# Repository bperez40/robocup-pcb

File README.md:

RoboCup PCB Repository
===========
Welcome to the Georgia Tech RoboJackets repository for management and storage of RoboCup's hardware files! Additional information about the team and current projects can be found on the [RoboJackets Website](http://www.robojackets.org/teams/robocup/) and the [RoboJacket Wiki](http://wiki.robojackets.org/w/RoboCup).

If you are a new member to the RoboCup electrical team and have never used *[git version control](http://git-scm.com/)* before, we highly recommend that you familiarize yourself with it by reading [this guide](https://github.com/RoboJackets/robocup-firmware/blob/master/doc/Git.md).

## Sponsor Thank You!
- Maxon (discount of EC45 and EC16 motors)
- PCBWay (donation of PCB fabrication runs)
- Texas Instruments (donation of ICs and SBCs)

## Prerequisites
- A computer configured with git [[Windows](https://windows.github.com)] [[Mac](https://mac.github.com/)]
- An installation of [EAGLE](http://www.cadsoftusa.com/)

## Using this Repository
Most CAD files found here are [EAGLE](http://www.cadsoftusa.com/) files. However, very few older archived files were created using [PCB](http://pcb.geda-project.org) (a program that is part of the [gEDA project](http://www.geda-project.org)). Users will find the following items here:
- Control, Kicker, Breakbeam, and Radio files

## Installation
Once your computer is setup with git, the following lines can be used on any operating system within a *[terminal](http://en.wikipedia.org/wiki/Computer_terminal)* configured with git. Users who are using a GUI interface for git should simply add the respective repositories through the interface.

### RoboCup Files
```
# Download the initial files
git clone https://github.com/robojackets/robocup-pcb

# Go into our new directory
cd robocup-pcb

# Download additional mtrain pcbs
git submodule update --init
```

### EAGLE Libraries
```
# Download the initial files
git clone https://github.com/RoboJackets/eagle-libraries.git

# Go into our new directory
cd eagle-libraries

# Follow the README.md file there
```

### Updating Repository
```
# Check which files will removed
git clean -d -x -n

# After being sure which files are deleted
git clean -d -x -f

# Download additional mtrain pcbs
git submodule update --init
```

## License

This project is licensed under the Apache License v2.0.  See the [LICENSE](LICENSE) file for more information.

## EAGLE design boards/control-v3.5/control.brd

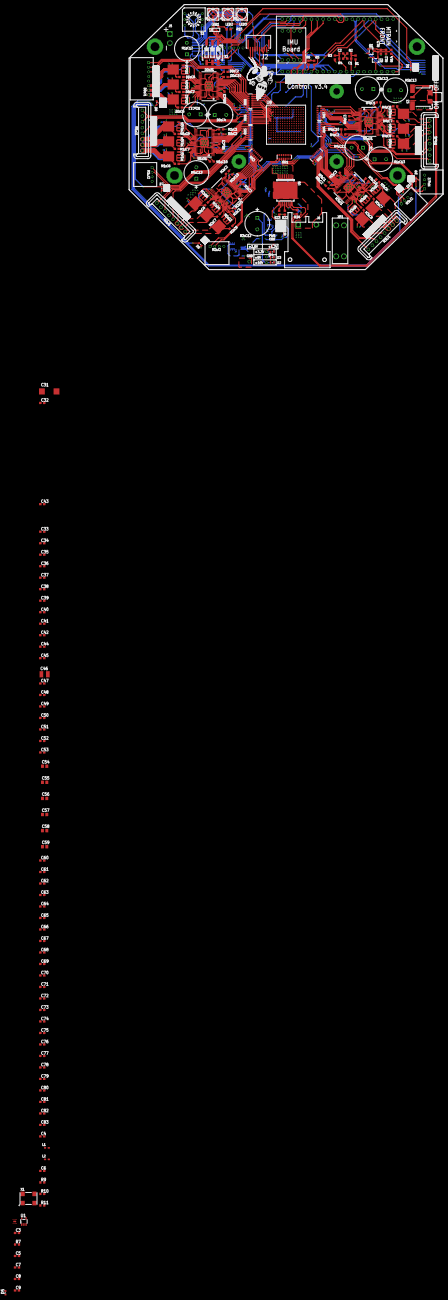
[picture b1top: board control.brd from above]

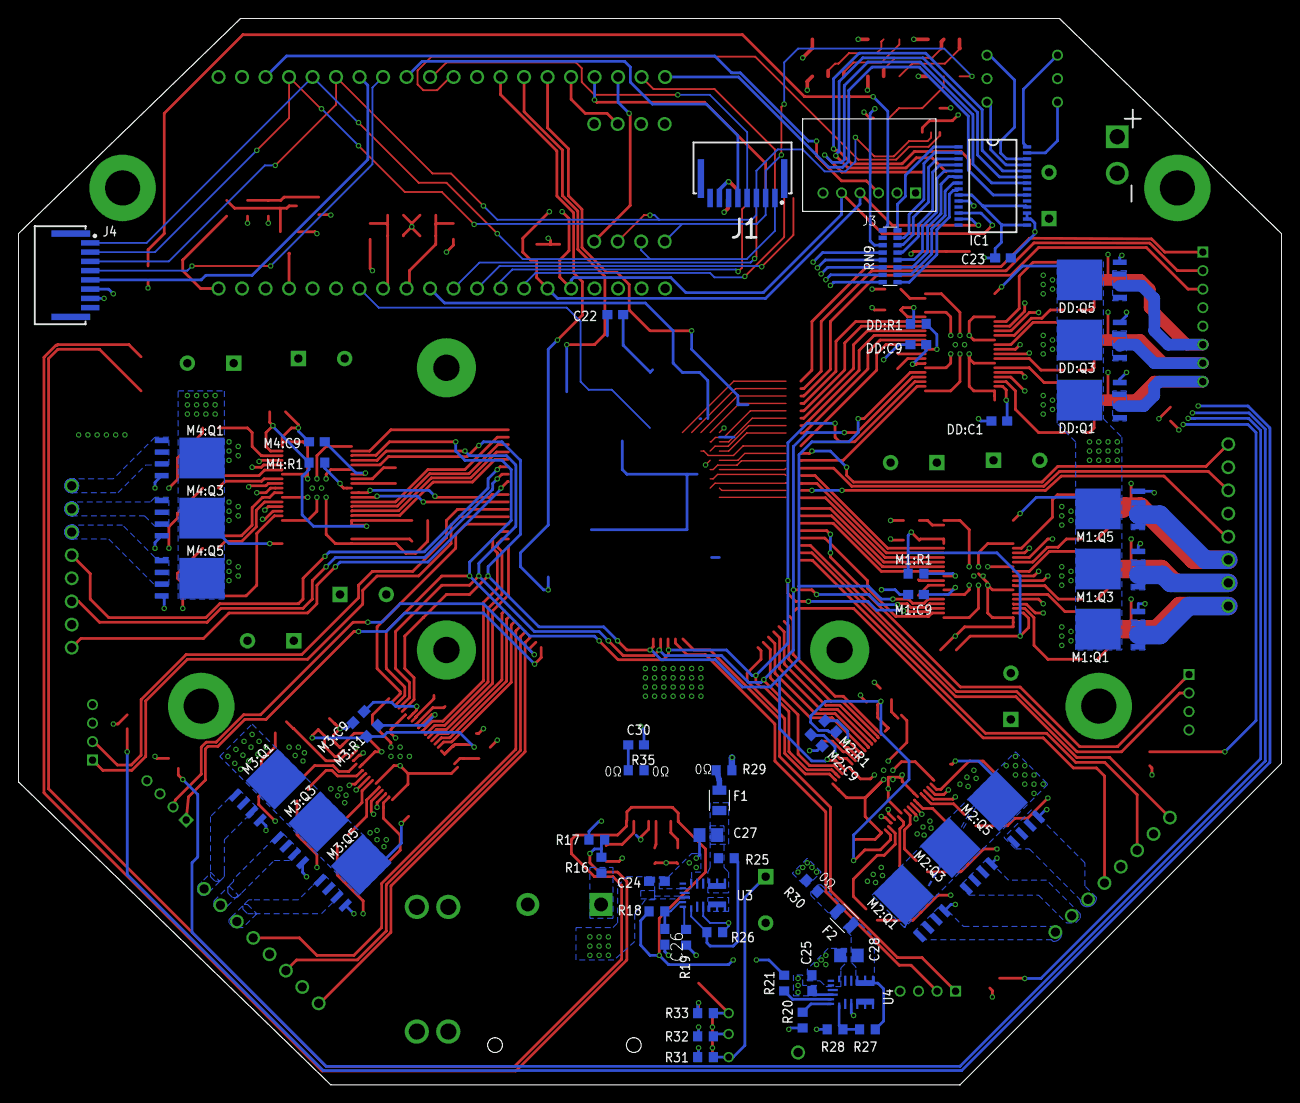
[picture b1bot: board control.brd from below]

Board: 6 copper layers, 136.5 x 115.2 mm, 264 parts (59 on the bottom side), 305 nets.

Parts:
C1: 0.1uF 50V; C0603
C2, C4, C22, C23: 0.1uF; C0603
C3, C8, C30: 1uF; C0603
C5, C7: 1uF X7R; C0603
C6, C38, C39, C40, C41, C42, C43, C44, C45, C47, C48, C49, C50, C51, C61, C62, C63, C64, C65, C66, C67, C68, C69, C70, C71, C72, C76, C77, C80, C81: 0.47uF; C0603
C9, C32, C33, C34, C35, C36, C37, C52, C53, C60, C73, C74, C75, C78, C79, C82, C83: 4.7uF; C0603
C24, C25: 10uF; C0603
C26: 2.2uF 50V; C0603
C27, C28: 22uF 16V; C0805
C31: 330uF; D/7343-31R
C46: 100uF; C1210
C54, C55, C56, C57, C58, C59: 47uF; C0805
D1, D5, D6, D7, D8, D9, D10: RED; CHIP-LED0603
D2, D3, D4: GREEN; CHIP-LED0603
DD:C1, DD:C2: 1uF; C0603
DD:C3: 0.022uF 50V; C0603
DD:C4: ECA-1HHG221; CAP_PAN_10X12.5
DD:C6, DD:C7, DD:C8, DD:C10: 0.1uF 50V; C0603
DD:C9: 2.2uF 50V; C0603
DD:J1: 8-PIN_2MM-H; 2MM-8-H
DD:Q1, DD:Q2, DD:Q3, DD:Q4, DD:Q5, DD:Q6: IRFH7545; PQFN_5X6_E
DD:R1: 10k; R0603
DD:U1: DRV8303DCA; TSSOP-48_PAD
F1, F2: 2A; FUSC2113X75
IC1: MCP23017-E/SS; SSOP-28
J1, J2, J4: HFW8R-1ST
J3: 6-PIN_2MM-H; 2MM-6-H
J5: 2-PIN-KICKERS; B2P_SMALL
J6: DF22-2; DF22-2-H
KIT1: MTRAIN; MTRAIN-KIT
KIT2: IMU
L1, L2: 60Ohm@100MHz; L0603
LED1, LED2, LED3: APA102C-5050; APA102_5050
M1:C1, M1:C2, M2:C1, M2:C2, M3:C1, M3:C2, M4:C1, M4:C2: 1uF; C0603
M1:C3, M2:C3, M3:C3, M4:C3: 0.022uF 50V; C0603
M1:C6, M1:C7, M1:C8, M1:C10, M2:C6, M2:C7, M2:C8, M2:C10, M3:C6, M3:C7, M3:C8, M3:C10, M4:C6, M4:C7, M4:C8, M4:C10: 0.1uF 50V; C0603
M1:C9, M2:C9, M3:C9, M4:C9: 2.2uF 50V; C0603
M1:C12, M1:C13, M2:C12, M2:C13, M3:C12, M3:C13, M4:C12, M4:C13: ECA-1HHG221; CAP_PAN_10X12.5
M1:J1, M2:J1, M3:J1, M4:J1: MKS-1658
M1:J2, M2:J2, M3:J2, M4:J2: 4-PIN_2MM-H; 2MM-4-H
M1:Q1, M1:Q2, M1:Q3, M1:Q4, M1:Q5, M1:Q6, M2:Q1, M2:Q2, M2:Q3, M2:Q4, M2:Q5, M2:Q6, M3:Q1, M3:Q2, M3:Q3, M3:Q4, M3:Q5, M3:Q6, M4:Q1, M4:Q2, M4:Q3, M4:Q4, M4:Q5, M4:Q6: IRFH7545; PQFN_5X6_E
M1:R1, M2:R1, M3:R1, M4:R1: 10k; R0603
M1:U1, M2:U1, M3:U1, M4:U1: DRV8303DCA; TSSOP-48_PAD
Q1, Q2: BSS806NH6327XTSA1; SOT-23-3
R1: 68k 1%; R0603
R2, R3, R4: 10k 1%; R0603
R5, R6, R9, R10: 4.7k; R0603
R7, R29, R30, R35: 0; R0603
R11: 330; R0603
R12, R22: 10k; R0603
R13, R14, R17: 100k; R0603
R15: 50k; R0603
R16: 270k; R0603
R18, R21: 150k; R0603
R19: 43.2k; R0603
R20: 29.4k; R0603
R23, R24, R31, R32, R33: 1k; R0603
R25, R27: 160k 1%; R0603
R26: 30.1k 1%; R0603
R28: 51.0k 1%; R0603
RN1, RN2, RN3, RN4, RN5, RN6, RN7, RN8, RN9: 330; RA-8_2506
S1: 94HCB16T; HEX
S2: 219-03; CTS-219-03
S3: 34EWMSP12M6RT
U1: MCP1824T-1802E/OT; SOT-23-5
U2: SN74AHC1G125; SOT-23-5
U3, U4: MPM3620GQV-P
U5: VND5E006ASPTR-E; POWERSO-16
U6: MIC47100-1.0YML-TR; DFN8_2X2MM
U8: XC7A35T-1FTG256C; BGA256C100P16X16_1700X1700X155
U$1: ERR-DRIB
U$2: ROBOJACKETS
U$3: MOTOR-1
U$4: DRIBBLER
U$5: MOTOR-2
U$6: MOTOR-3
U$7: MOTOR-4
U$8: ERR-M1
U$9: KICKER
U$11: ROBOBUZZ_1.0X2
U$12: ERR-M2
U$13: ERR-M3
U$14: ERR-M4
U$15: ERR-KICK
X1: ASV-50.000MHZ-E-T; ASV
XF1: 30A; 3557-2

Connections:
5V-LED: D3.A, R32.2
5V-LED1: D4.A, R33.2
18.5V-LED: D2.A, R31.1
!CS!-DOT: KIT1.P$11, U2.1
!CS!-FPGA: KIT1.P$31, U8.K12
!CS!-ICM: KIT1.P$18, KIT2.4
!CS!-KICKER: J4.4, KIT1.P$8
!CS!-RADIO: J2.5, KIT1.P$17
!CS!-SPI: J1.4, KIT1.P$10
!RST!-I2C: J3.2, RN9.11
!RST!-KICKER: J4.5, KIT1.P$7
!RST!-NETWORK: KIT1.!RST, Q2.3
!RST!-RADIO: J2.6, KIT1.P$19
!RST!-SPI: J1.5, KIT1.P$9
!RST!_CTRL: Q1.3, Q2.1, R14.1
+1.0V: C31.+, C32.1, C33.1, C34.1, C35.1, C36.1, C37.1, C38.1, C39.1, C40.1, C41.1, C42.1, C43.1, C44.1, C45.1, C46.1, C47.1, C48.1, R7.2, U8.E10, U8.F7, U8.F9, U8.F11, U8.G6, U8.H9, U8.J6, U8.K9, U8.L8
+1.8V: L2.2, R35.2
+3.3V: C3.1, C7.1, C8.1, C56.1, C61.1, C65.1, C80.1, C81.1, C82.1, C83.1, D5.A, J1.8, R9.2, R10.2, R11.2, U6.P$2, U6.P$5, U6.P$6, U8.E7, U8.L16, U8.M9, U8.M10, U8.M11, U8.M13, U8.N10, U8.P7, U8.R14, U8.T11
+3.3V-FUSE: C28.1, F2.1, R27.2, U4.789
+5V: DD:J1.5, J2.1, J3.1, KIT1.VIN, LED1.1, LED2.1, LED3.1, M1:J1.4, M1:J2.4, M2:J1.4, M2:J2.4, M3:J1.4, M3:J2.4, M4:J1.4, M4:J2.4, R3.1, R29.2, R32.1
+5V-FUSE: C27.1, F1.1, R25.2, U3.789
+18.5V: C24.1, C25.1, DD:C4.1, DD:Q1.5678, DD:Q3.5678, DD:Q5.5678, DD:U1.25, M1:C12.1, M1:C13.1, M1:Q1.5678, M1:Q3.5678, M1:Q5.5678, M1:U1.25, M2:C12.1, M2:C13.1, M2:Q1.5678, M2:Q3.5678, M2:Q5.5678, M2:U1.25, M3:C12.1, M3:C13.1, M3:Q1.5678, M3:Q3.5678, M3:Q5.5678, M3:U1.25, M4:C12.1, M4:C13.1, M4:Q1.5678, M4:Q3.5678, M4:Q5.5678, M4:U1.25, R1.1, R31.2, U3.16, U4.16, XF1.3, XF1.4
AAM: R19.2, U3.18
AAM1: R20.2, U4.18
BATT_PWR_AVAIL: Q1.1, R12.1, R13.2
CS1: R23.2, U5.10
CS2: R24.2, U5.15
CS-DIS: R22.2, U5.12
DD-!CS: DD:U1.4, RN6.11
DD-A-H: DD:U1.13, RN6.9
DD-A-L: DD:U1.14, RN8.16
DD-B-H: DD:U1.15, RN8.15
DD-B-L: DD:U1.16, RN8.14
DD-C-H: DD:U1.17, RN8.13
DD-C-L: DD:U1.18, RN8.12
DD-H1: DD:J1.3, RN8.11
DD-H2: DD:J1.2, RN8.10
DD-H3: DD:J1.1, RN8.9
DD:AVDD: DD:C2.1, DD:U1.23
DD:BST-A: DD:C6.1, DD:U1.44
DD:BST-B: DD:C7.1, DD:U1.39
DD:BST-C: DD:C8.1, DD:U1.34
DD:CP1: DD:C3.1, DD:U1.10
DD:CP2: DD:C3.2, DD:U1.11
DD:EN-GATE: DD:R1.2, DD:U1.12
DD:GH-A: DD:Q1.4, DD:U1.43
DD:GH-B: DD:Q3.4, DD:U1.38
DD:GH-C: DD:Q5.4, DD:U1.33
DD:GL-A: DD:Q2.4, DD:U1.41
DD:GL-B: DD:Q4.4, DD:U1.36
DD:GL-C: DD:Q6.4, DD:U1.31
DD:GVDD: DD:C9.1, DD:U1.9
DD:PHASE-A: DD:C6.2, DD:J1.8, DD:Q1.1, DD:Q1.2, DD:Q1.3, DD:Q2.5678, DD:U1.42
DD:PHASE-B: DD:C7.2, DD:J1.7, DD:Q3.1, DD:Q3.2, DD:Q3.3, DD:Q4.5678, DD:U1.37
DD:PHASE-C: DD:C8.2, DD:J1.6, DD:Q5.1, DD:Q5.2, DD:Q5.3, DD:Q6.5678, DD:U1.32
DIP-1: IC1.22, S2.1
DIP-2: IC1.23, S2.2
DIP-3: IC1.24, S2.3
DOT-CLK-1: LED1.5, R15.2, U2.4
DOT-CLK-1-2: LED1.2, LED2.5
DOT-CLK-2-3: LED2.2, LED3.5
DOT-MOSI-1-2: LED1.3, LED2.4
DOT-MOSI-2-3: LED2.3, LED3.4
EN: C26.1, R18.2, U3.17
EN1: R21.2, U4.17
EN-PWR: R18.1, R21.1, S3.2, U5.9, U5.16
EN-PWR-PRE: R16.1, R17.2, S3.1
EXT_SCK: U8.A9, X1.3
FB: R25.1, R26.2, U3.1
FB1: R27.1, R28.2, U4.1
FPGA-DONE: KIT1.P$15, R11.1, U8.H10
FPGA-INIT: KIT1.P$14, R9.1, U8.K10
FPGA-PROG: KIT1.P$13, R10.1, U8.L9
GND: C1.2, C2.2, C3.2, C5.2, C7.2, C8.2, C9.2, C22.2, C23.2, C24.2, C25.2, C26.2, C27.2, C28.2, C30.2, C31.-, C32.2, C33.2, C34.2, C35.2, C36.2, C37.2, C38.2, C39.2, C40.2, C41.2, C42.2, C43.2, C44.2, C45.2, C46.2, C47.2, C48.2, C49.2, C50.2, C51.2, C52.2, C53.2, C54.2, C55.2, C56.2, C57.2, C58.2, C59.2, C60.2, C61.2, C62.2, C63.2, C64.2, C65.2, C66.2, C67.2, C68.2, C69.2, C70.2, C71.2, C72.2, C73.2, C74.2, C75.2, C76.2, C77.2, C78.2, C79.2, C80.2, C81.2, C82.2, C83.2, D2.C, D3.C, D4.C, DD:C1.2, DD:C2.2, DD:C4.2, DD:C9.2, DD:C10.2, DD:J1.4, DD:Q2.1, DD:Q2.2, DD:Q2.3, DD:Q4.1, DD:Q4.2, DD:Q4.3, DD:Q6.1, DD:Q6.2, DD:Q6.3, DD:U1.3, DD:U1.8, DD:U1.20, DD:U1.24, DD:U1.30, DD:U1.35, DD:U1.40, DD:U1.46, DD:U1.47, DD:U1.48, DD:U1.PAD, IC1.10, IC1.16, IC1.17, J1.7, J2.2, J3.6, J4.6, J5.1, J6.2, KIT1.GND, KIT2.5, L1.2, LED1.6, LED2.6, LED3.6, M1:C1.2, M1:C2.2, M1:C9.2, M1:C10.2, M1:C12.2, M1:C13.2, M1:J1.2, M1:J2.3, M1:Q2.1, M1:Q2.2, M1:Q2.3, M1:Q4.1, M1:Q4.2, M1:Q4.3, M1:Q6.1, M1:Q6.2, M1:Q6.3, M1:U1.3, M1:U1.8, M1:U1.24, M1:U1.30, M1:U1.35, M1:U1.40, M1:U1.46, M1:U1.47, M1:U1.48, M1:U1.PAD, M2:C1.2, M2:C2.2, M2:C9.2, M2:C10.2, M2:C12.2, M2:C13.2, M2:J1.2, M2:J2.3, M2:Q2.1, M2:Q2.2, M2:Q2.3, M2:Q4.1, M2:Q4.2, M2:Q4.3, M2:Q6.1, M2:Q6.2, M2:Q6.3, M2:U1.3, M2:U1.8, M2:U1.24, M2:U1.30, M2:U1.35, M2:U1.40, M2:U1.46, M2:U1.47, M2:U1.48, M2:U1.PAD, M3:C1.2, M3:C2.2, M3:C9.2, M3:C10.2, M3:C12.2, M3:C13.2, M3:J1.2, M3:J2.3, M3:Q2.1, M3:Q2.2, M3:Q2.3, M3:Q4.1, M3:Q4.2, M3:Q4.3, M3:Q6.1, M3:Q6.2, M3:Q6.3, M3:U1.3, M3:U1.8, M3:U1.24, M3:U1.30, M3:U1.35, M3:U1.40, M3:U1.46, M3:U1.47, M3:U1.48, M3:U1.PAD, M4:C1.2, M4:C2.2, M4:C9.2, M4:C10.2, M4:C12.2, M4:C13.2, M4:J1.2, M4:J2.3, M4:Q2.1, M4:Q2.2, M4:Q2.3, M4:Q4.1, M4:Q4.2, M4:Q4.3, M4:Q6.1, M4:Q6.2, M4:Q6.3, M4:U1.3, M4:U1.8, M4:U1.24, M4:U1.30, M4:U1.35, M4:U1.40, M4:U1.46, M4:U1.47, M4:U1.48, M4:U1.PAD, Q1.2, Q2.2, R2.2, R4.2, R13.1, R15.1, R17.1, R19.1, R20.1, R22.1, R23.1, R24.1, R26.1, R28.1, S1.C1, S1.C2, S2.4, S2.5, S2.6, S3.3, S3.LEG1, S3.LEG3, U1.2, U2.3, U3.3, U3.12, U3.13, U3.14, U4.3, U4.12, U4.13, U4.14, U5.13, U6.P$4, U8.A1, U8.A11, U8.B8, U8.C5, U8.C15, U8.D2, U8.D12, U8.E9, U8.F6, U8.F8, U8.F10, U8.F16, U8.G3, U8.G9, U8.G13, U8.H6, U8.H8, U8.J7, U8.J9, U8.J11, U8.K4, U8.K6, U8.K7, U8.K8, U8.K14, U8.L1, U8.L11, U8.L15, U8.M8, U8.N5, U8.N15, U8.P2, U8.P12, U8.R9, U8.T6, U8.T16, X1.2
GNDADC: C4.2, C6.2, L1.1, U8.G7, U8.H7, U8.J8
GPB0: IC1.1, RN9.8
GPB1: IC1.2, RN9.7
GPB2: IC1.3, RN9.6
GPB3: IC1.4, RN9.5
GPB4: IC1.5, RN9.4
GPB5: IC1.6, RN9.3
GPB6: IC1.7, RN9.2
GPB7: IC1.8, RN9.1
HEX-0: IC1.28, S1.1
HEX-1: IC1.25, S1.2
HEX-2: IC1.27, S1.4
HEX-3: IC1.26, S1.8
INT-I2C: J3.3, KIT1.P$3
INT-ICM: KIT1.P$16, KIT2.6
INT-IO: IC1.20, KIT1.P$20
INT-RADIO: J2.4, KIT1.P$30
INT-SPI: J1.6, KIT1.P$12
LED-DD: D8.C, RN9.16
LED-KICK: D1.C, RN9.9
LED-M1: D7.C, RN9.15
LED-M2: D6.C, RN9.14
LED-M3: D10.C, RN9.13
LED-M4: D9.C, RN9.12
M1-!CS: M1:U1.4, RN5.13
M1-A-H: M1:U1.15, RN5.9
M1-A-L: M1:U1.16, RN6.16
M1-B-H: M1:U1.13, RN5.11
M1-B-L: M1:U1.14, RN5.10
M1-C-H: M1:U1.17, RN6.14
M1-C-L: M1:U1.18, RN6.13
M1-ENC-A: M1:J2.2, RN5.14
M1-ENC-B: M1:J2.1, RN5.12
M1-H1: M1:J1.1, RN6.10
M1-H2: M1:J1.3, RN6.12
M1-H3: M1:J1.5, RN6.15
M1:+3.3V: M1:C1.1, M1:C10.1, M1:R1.1, M1:U1.19, M1:U1.20, M1:U1.45
M1:AVDD: M1:C2.1, M1:U1.23
M1:BST-A: M1:C6.1, M1:U1.44
M1:BST-B: M1:C7.1, M1:U1.39
M1:BST-C: M1:C8.1, M1:U1.34
M1:CP1: M1:C3.1, M1:U1.10
M1:CP2: M1:C3.2, M1:U1.11
M1:EN-GATE: M1:R1.2, M1:U1.12
M1:GH-A: M1:Q1.4, M1:U1.43
M1:GH-B: M1:Q3.4, M1:U1.38
M1:GH-C: M1:Q5.4, M1:U1.33
M1:GL-A: M1:Q2.4, M1:U1.41
M1:GL-B: M1:Q4.4, M1:U1.36
M1:GL-C: M1:Q6.4, M1:U1.31
M1:GVDD: M1:C9.1, M1:U1.9
M1:PHASE-A: M1:C7.2, M1:J1.7, M1:Q3.1, M1:Q3.2, M1:Q3.3, M1:Q4.5678, M1:U1.37
M1:PHASE-B: M1:C6.2, M1:J1.8, M1:Q1.1, M1:Q1.2, M1:Q1.3, M1:Q2.5678, M1:U1.42
M1:PHASE-C: M1:C8.2, M1:J1.6, M1:Q5.1, M1:Q5.2, M1:Q5.3, M1:Q6.5678, M1:U1.32
M2-!CS: M2:U1.4, RN3.16
M2-A-H: M2:U1.15, RN3.13
M2-A-L: M2:U1.16, RN3.12
M2-B-H: M2:U1.13, RN3.15
M2-B-L: M2:U1.14, RN3.14
M2-C-H: M2:U1.17, RN3.11
M2-C-L: M2:U1.18, RN3.10
M2-ENC-A: M2:J2.2, RN1.10
M2-ENC-B: M2:J2.1, RN1.9
M2-H1: M2:J1.1, RN5.15
M2-H2: M2:J1.3, RN5.16
M2-H3: M2:J1.5, RN3.9
M2:+3.3V: M2:C1.1, M2:C10.1, M2:R1.1, M2:U1.19, M2:U1.20, M2:U1.45
M2:AVDD: M2:C2.1, M2:U1.23
M2:BST-A: M2:C6.1, M2:U1.44
M2:BST-B: M2:C7.1, M2:U1.39
M2:BST-C: M2:C8.1, M2:U1.34
M2:CP1: M2:C3.1, M2:U1.10
M2:CP2: M2:C3.2, M2:U1.11
M2:EN-GATE: M2:R1.2, M2:U1.12
M2:GH-A: M2:Q1.4, M2:U1.43
M2:GH-B: M2:Q3.4, M2:U1.38
M2:GH-C: M2:Q5.4, M2:U1.33
M2:GL-A: M2:Q2.4, M2:U1.41
M2:GL-B: M2:Q4.4, M2:U1.36
M2:GL-C: M2:Q6.4, M2:U1.31
M2:GVDD: M2:C9.1, M2:U1.9
M2:PHASE-A: M2:C7.2, M2:J1.7, M2:Q3.1, M2:Q3.2, M2:Q3.3, M2:Q4.5678, M2:U1.37
M2:PHASE-B: M2:C6.2, M2:J1.8, M2:Q1.1, M2:Q1.2, M2:Q1.3, M2:Q2.5678, M2:U1.42
M2:PHASE-C: M2:C8.2, M2:J1.6, M2:Q5.1, M2:Q5.2, M2:Q5.3, M2:Q6.5678, M2:U1.32
M3-!CS: M3:U1.4, RN4.12
M3-A-H: M3:U1.15, RN4.9
M3-A-L: M3:U1.16, RN2.16
M3-B-H: M3:U1.13, RN4.11
M3-B-L: M3:U1.14, RN4.10
M3-C-H: M3:U1.17, RN2.15
M3-C-L: M3:U1.18, RN2.14
M3-ENC-A: M3:J2.2, RN2.10
M3-ENC-B: M3:J2.1, RN2.9
M3-H1: M3:J1.1, RN2.11
M3-H2: M3:J1.3, RN2.12
M3-H3: M3:J1.5, RN2.13
M3:+3.3V: M3:C1.1, M3:C10.1, M3:R1.1, M3:U1.19, M3:U1.20, M3:U1.45
M3:AVDD: M3:C2.1, M3:U1.23
M3:BST-A: M3:C6.1, M3:U1.44
M3:BST-B: M3:C7.1, M3:U1.39
M3:BST-C: M3:C8.1, M3:U1.34
M3:CP1: M3:C3.1, M3:U1.10
M3:CP2: M3:C3.2, M3:U1.11
M3:EN-GATE: M3:R1.2, M3:U1.12
M3:GH-A: M3:Q1.4, M3:U1.43
M3:GH-B: M3:Q3.4, M3:U1.38
M3:GH-C: M3:Q5.4, M3:U1.33
M3:GL-A: M3:Q2.4, M3:U1.41
M3:GL-B: M3:Q4.4, M3:U1.36
M3:GL-C: M3:Q6.4, M3:U1.31
M3:GVDD: M3:C9.1, M3:U1.9
M3:PHASE-A: M3:C7.2, M3:J1.7, M3:Q3.1, M3:Q3.2, M3:Q3.3, M3:Q4.5678, M3:U1.37
M3:PHASE-B: M3:C6.2, M3:J1.8, M3:Q1.1, M3:Q1.2, M3:Q1.3, M3:Q2.5678, M3:U1.42
M3:PHASE-C: M3:C8.2, M3:J1.6, M3:Q5.1, M3:Q5.2, M3:Q5.3, M3:Q6.5678, M3:U1.32
M4-!CS: M4:U1.4, RN7.16
M4-A-H: M4:U1.15, RN7.15
M4-A-L: M4:U1.16, RN7.14
M4-B-H: M4:U1.13, RN4.16
M4-B-L: M4:U1.14, RN4.15
M4-C-H: M4:U1.17, RN7.13
M4-C-L: M4:U1.18, RN7.12
M4-ENC-A: M4:J2.2, RN4.14
M4-ENC-B: M4:J2.1, RN4.13
M4-H1: M4:J1.1, RN7.9
M4-H2: M4:J1.3, RN7.10
M4-H3: M4:J1.5, RN7.11
M4:+3.3V: M4:C1.1, M4:C10.1, M4:R1.1, M4:U1.19, M4:U1.20, M4:U1.45
M4:AVDD: M4:C2.1, M4:U1.23
M4:BST-A: M4:C6.1, M4:U1.44
M4:BST-B: M4:C7.1, M4:U1.39
M4:BST-C: M4:C8.1, M4:U1.34
M4:CP1: M4:C3.1, M4:U1.10
M4:CP2: M4:C3.2, M4:U1.11
M4:EN-GATE: M4:R1.2, M4:U1.12
M4:GH-A: M4:Q1.4, M4:U1.43
M4:GH-B: M4:Q3.4, M4:U1.38
M4:GH-C: M4:Q5.4, M4:U1.33
M4:GL-A: M4:Q2.4, M4:U1.41
M4:GL-B: M4:Q4.4, M4:U1.36
M4:GL-C: M4:Q6.4, M4:U1.31
M4:GVDD: M4:C9.1, M4:U1.9
M4:PHASE-A: M4:C7.2, M4:J1.7, M4:Q3.1, M4:Q3.2, M4:Q3.3, M4:Q4.5678, M4:U1.37
M4:PHASE-B: M4:C6.2, M4:J1.8, M4:Q1.1, M4:Q1.2, M4:Q1.3, M4:Q2.5678, M4:U1.42
M4:PHASE-C: M4:C8.2, M4:J1.6, M4:Q5.1, M4:Q5.2, M4:Q5.3, M4:Q6.5678, M4:U1.32
MISO: J1.1, J4.1, KIT1.P$5, KIT2.2
MISO-AUX: DD:U1.6, M1:U1.6, M2:U1.6, M3:U1.6, M4:U1.6, RN1.12
MISO-FPGA: KIT1.P$35, U8.J13
MISO-RADIO: J2.3, KIT1.P$28
MOSI: J1.2, J4.2, KIT1.P$4, KIT2.1, LED1.4
MOSI-AUX: DD:U1.5, M1:U1.5, M2:U1.5, M3:U1.5, M4:U1.5, RN1.11
MOSI-FPGA: KIT1.P$36, U8.J14
MOSI-RADIO: J2.7, KIT1.P$27
unnamed: F2.2, R30.1
unnamed: F1.2, R29.1
unnamed: C5.1, R7.1, U6.P$7, U6.P$8, U6.P$9
PWR-ERR: D5.C, U1.4
SCK: J1.3, J4.3, KIT1.P$6, KIT2.3, U2.2
SCK-AUX: DD:U1.7, M1:U1.7, M2:U1.7, M3:U1.7, M4:U1.7, RN1.13
SCK-FPGA: KIT1.P$34, U8.E8
SCK-RADIO: J2.8, KIT1.P$29
SCL: IC1.12, J3.5, KIT1.P$25, R6.1
SDA: IC1.13, J3.4, KIT1.P$26, R5.1
SENSE-BATTERY: C1.1, KIT1.P$33, R1.2, R2.1
SENSE-VIN: C2.1, KIT1.P$32, R3.2, R4.1
T1: RN2.1, U8.M16
T2: RN2.2, U8.N16
T3: RN2.4, U8.P15
T4: RN2.3, U8.P16
T5: RN2.6, U8.R15
T6: RN2.5, U8.R16
T7: RN2.8, U8.T14
T8: RN2.7, U8.T15
T9: RN7.1, U8.A12
T10: RN7.2, U8.A13
T11: RN7.3, U8.A14
T12: RN7.8, U8.C14
T13: RN7.7, U8.B14
T14: RN7.6, U8.B15
T15: RN7.4, U8.A15
T16: RN7.5, U8.B16
T17: RN4.8, U8.J16
T18: RN4.7, U8.J15
T19: RN4.5, U8.G16
T20: RN4.6, U8.H16
T21: RN4.2, U8.E15
T22: RN4.4, U8.F15
T23: RN4.1, U8.D16
T24: RN4.3, U8.E16
T25: RN8.8, U8.A5
T26: RN8.7, U8.A4
T27: RN8.6, U8.A3
T28: RN8.2, U8.C2
T29: RN8.4, U8.B2
T30: RN8.5, U8.A2
T31: RN8.1, U8.C1
T32: RN8.3, U8.B1
T33: RN6.8, U8.C3
T34: RN6.6, U8.E2
T35: RN6.7, U8.D1
T36: RN6.1, U8.H1
T37: RN6.2, U8.G1
T38: RN6.3, U8.G2
T39: RN6.5, U8.E1
T40: RN6.4, U8.F2
T41: RN5.6, U8.K2
T42: RN5.4, U8.L2
T43: RN5.7, U8.J1
T44: RN5.5, U8.K1
T45: RN5.8, U8.H2
T46: RN5.3, U8.M2
T47: RN5.2, U8.M1
T48: RN5.1, U8.N1
T49: RN3.2, U8.T3
T50: RN3.1, U8.T4
T51: RN3.3, U8.T2
T52: RN3.4, U8.R3
T53: RN3.5, U8.R1
T54: RN3.6, U8.R2
T55: RN3.7, U8.P1
T56: RN3.8, U8.N2
T57: RN1.8, U8.T5
T58: RN1.4, U8.T10
T59: RN1.5, U8.T9
T60: RN1.6, U8.T8
T61: RN1.7, U8.T7
VBATT: J5.2, U5.1, U5.2, U5.3, U5.4, U5.5, U5.6, U5.7, U5.8, XF1.1, XF1.2
VCCAUX: C4.1, C6.1, C49.1, C50.1, C51.1, C52.1, C53.1, C54.1, L2.1, U8.G8, U8.G10, U8.J10, U8.K11, U8.L10
VCCO_0: C9.1, C22.1, C23.1, C55.1, C57.1, C58.1, C59.1, C60.1, C62.1, C63.1, C64.1, C66.1, C67.1, C68.1, C69.1, C70.1, C71.1, C72.1, C73.1, C74.1, C75.1, C76.1, C77.1, C78.1, C79.1, D1.A, D6.A, D7.A, D8.A, D9.A, D10.A, DD:C1.1, DD:C10.1, DD:R1.1, DD:U1.19, DD:U1.45, IC1.9, IC1.15, IC1.18, J4.7, KIT2.8, R5.2, R6.2, R12.2, R30.2, R33.1, U1.1, U1.3, U2.5, U8.A6, U8.A16, U8.B3, U8.B13, U8.C10, U8.D7, U8.E4, U8.E14, U8.F1, U8.H15, U8.J2, U8.J12, U8.L6, U8.M3, U8.R4, U8.T1, X1.1, X1.4
VIN: J6.1, R16.2, U5.17
V_MTRAIN: KIT1.VDD, R14.2
V_OUT: C30.1, R35.1, U1.5

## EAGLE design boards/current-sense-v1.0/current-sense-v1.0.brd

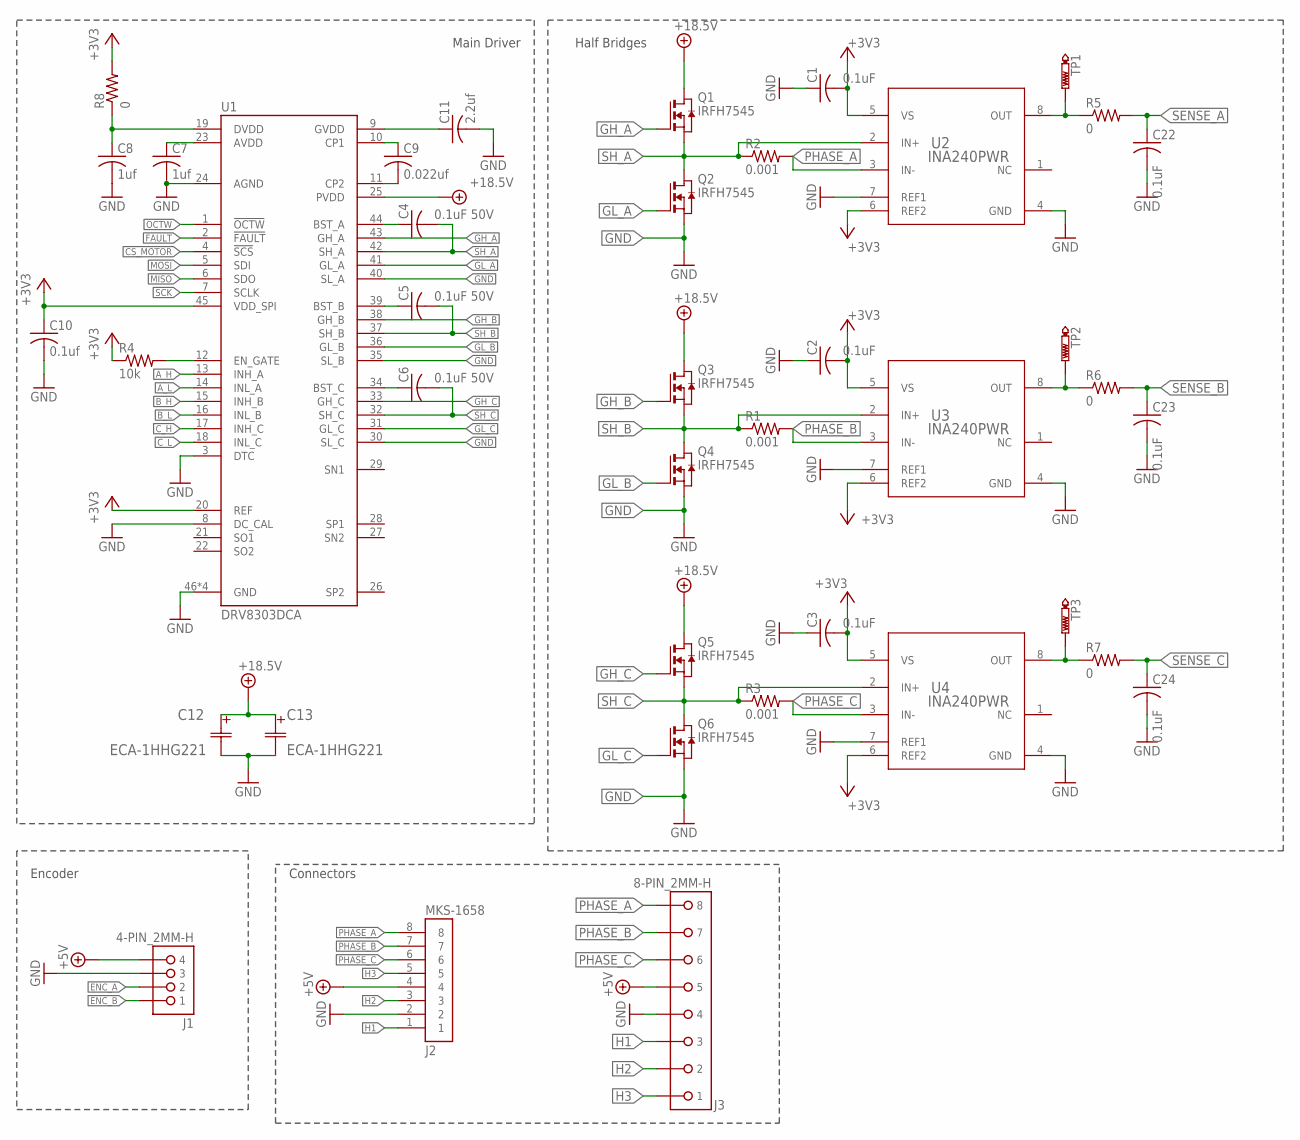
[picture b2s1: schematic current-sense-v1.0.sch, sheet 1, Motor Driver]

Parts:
C1, C2, C3, C22, C23, C24: 0.1uF; C0603
C4, C5, C6: 0.1uF 50V; C0603
C7, C8: 1uf; C0603
C9: 0.022uf; C0603
C10: 0.1uf; C0603
C11: 2.2uf; C0603
C12, C13: ECA-1HHG221; CAP_PAN_10X12.5
J1: 4-PIN_2MM-H; 2MM-4-H
J2: MKS-1658
J3: 8-PIN_2MM-H; 2MM-8-H
Q1, Q2, Q3, Q4, Q5, Q6: IRFH7545; PQFN_5X6_E
R1, R2, R3: 0.001; R2512
R4: 10k; R0603
R5, R6, R7, R8: 0; R0603
TP1, TP2, TP3: PTR1PAD1-13; P1-13
U1: DRV8303DCA; TSSOP-48_PAD
U2, U3, U4: INA240PWR; PW0008A_N

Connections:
+3V3: C1.2, C2.2, C3.2, C10.1, R4.1, R8.2, U1.20 (REF), U1.45 (VDD_SPI), U2.5 (VS), U2.6 (REF2), U3.5 (VS), U3.6 (REF2), U4.5 (VS), U4.6 (REF2); also elsewhere on the board
+5V: J1.4, J2.4, J3.5; also elsewhere on the board
+18.5V: C12.1 (11), C13.1 (11), Q1.5678 (D), Q3.5678 (D), Q5.5678 (D), U1.25 (PVDD); also elsewhere on the board
AVDD: C7.1, U1.23 (AVDD)
A_H: U1.13 (INH_A); also elsewhere on the board
A_L: U1.14 (INL_A); also elsewhere on the board
BST_A: C4.1, U1.44 (BST_A)
BST_B: C5.1, U1.39 (BST_B)
BST_C: C6.1, U1.34 (BST_C)
B_H: U1.15 (INH_B); also elsewhere on the board
B_L: U1.16 (INL_B); also elsewhere on the board
CP1: C9.1, U1.10 (CP1)
CP2: C9.2, U1.11 (CP2)
CS_MOTOR: U1.4 (!SCS); also elsewhere on the board
C_H: U1.17 (INH_C); also elsewhere on the board
C_L: U1.18 (INL_C); also elsewhere on the board
DVDD: C8.1, R8.1, U1.19 (DVDD)
ENC_A: J1.2; also elsewhere on the board
ENC_B: J1.1; also elsewhere on the board
EN_GATE: R4.2, U1.12 (EN_GATE)
FAULT: U1.2 (!FAULT)
GH_A: Q1.4 (G), U1.43 (GH_A)
GH_B: Q3.4 (G), U1.38 (GH_B)
GH_C: Q5.4 (G), U1.33 (GH_C)
GL_A: Q2.4 (G), U1.41 (GL_A)
GL_B: Q4.4 (G), U1.36 (GL_B)
GL_C: Q6.4 (G), U1.31 (GL_C)
GND: C1.1, C2.1, C3.1, C7.2, C8.2, C10.2, C11.2, C12.2 (22), C13.2 (22), C22.2, C23.2, C24.2, J1.3, J2.2, J3.4, Q2.1 (S), Q2.2 (S), Q2.3 (S), Q4.1 (S), Q4.2 (S), Q4.3 (S), Q6.1 (S), Q6.2 (S), Q6.3 (S), U1.3 (DTC), U1.8 (DC_CAL), U1.24 (AGND), U1.30 (SL_C), U1.35 (SL_B), U1.40 (SL_A), U1.46 (GND), U1.47 (GND), U1.48 (GND), U1.PAD (GND), U2.4 (GND), U2.7 (REF1), U3.4 (GND), U3.7 (REF1), U4.4 (GND), U4.7 (REF1); also elsewhere on the board
GVDD: C11.1, U1.9 (GVDD)
H1: J2.1, J3.3; also elsewhere on the board
H2: J2.3, J3.2; also elsewhere on the board
H3: J2.5, J3.1; also elsewhere on the board
MISO: U1.6 (SDO); also elsewhere on the board
MOSI: U1.5 (SDI); also elsewhere on the board
OCTW: U1.1 (!OCTW)
OUT_A: R5.1, TP1.TP, U2.8 (OUT)
OUT_B: R6.1, TP2.TP, U3.8 (OUT)
OUT_C: R7.1, TP3.TP, U4.8 (OUT)
PHASE_A: J2.8, J3.8, R2.2, U2.3 (IN-)
PHASE_B: J2.7, J3.7, R1.2, U3.3 (IN-)
PHASE_C: J2.6, J3.6, R3.2, U4.3 (IN-)
SCK: U1.7 (SCLK); also elsewhere on the board
SENSE_A: C22.1, R5.2; also elsewhere on the board
SENSE_B: C23.1, R6.2; also elsewhere on the board
SENSE_C: C24.1, R7.2; also elsewhere on the board
SH_A: C4.2, Q1.1 (S), Q1.2 (S), Q1.3 (S), Q2.5678 (D), R2.1, U1.42 (SH_A), U2.2 (IN+)
SH_B: C5.2, Q3.1 (S), Q3.2 (S), Q3.3 (S), Q4.5678 (D), R1.1, U1.37 (SH_B), U3.2 (IN+)
SH_C: C6.2, Q5.1 (S), Q5.2 (S), Q5.3 (S), Q6.5678 (D), R3.1, U1.32 (SH_C), U4.2 (IN+)

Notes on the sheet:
Main Driver
Encoder
Connectors
Half Bridges

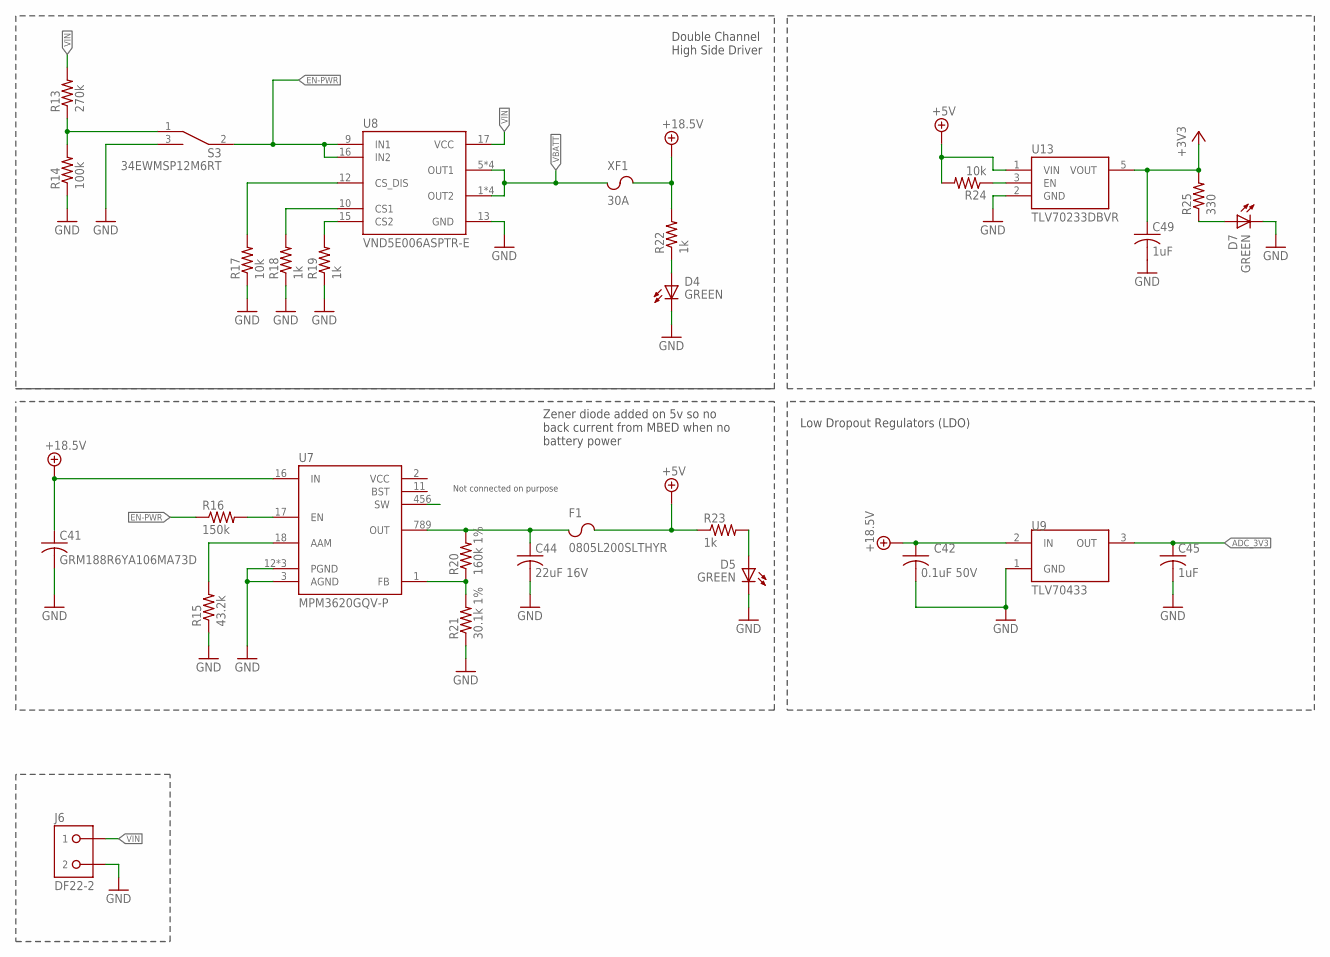
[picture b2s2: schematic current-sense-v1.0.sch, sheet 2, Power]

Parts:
C41: GRM188R6YA106MA73D; C0603
C42: 0.1uF 50V; C0603
C44: 22uF 16V; C0805
C45, C49: 1uF; C0603
D4, D5, D7: GREEN; CHIP-LED0603
F1: 0805L200SLTHYR; FUSC2113X75
J6: DF22-2; DF22-2-H
R13: 270k; R0603
R14: 100k; R0603
R15: 43.2k; R0603
R16: 150k; R0603
R17, R24: 10k; R0603
R18, R19, R22, R23: 1k; R0603
R20: 160k 1%; R0603
R21: 30.1k 1%; R0603
R25: 330; R0603
S3: 34EWMSP12M6RT
U7: MPM3620GQV-P; MPN MPM3620GQV-P; DIGIKEY 1589-1252-1-ND
U8: VND5E006ASPTR-E; POWERSO-16
U9: TLV70433; SOT-23-5
U13: TLV70233DBVR; SOT-23-5
XF1: 30A; 3557-2

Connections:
3.3V-EN: R24.1, U13.3 (EN)
3V3-LED: D7.A, R25.1
5V-LED: D5.A, R23.2
18.5V-LED: D4.A, R22.1
+3V3: C49.1, R25.2, U13.5 (VOUT); also elsewhere on the board
+5V: F1.2, R23.1, R24.2, U13.1 (VIN); also elsewhere on the board
+5V-FUSE: C44.1, F1.1, R20.2, U7.789 (OUT)
+18.5V: C41.1, C42.1, R22.2, U7.16 (IN), U9.2 (IN), XF1.3 (2), XF1.4 (2); also elsewhere on the board
AAM: R15.2, U7.18 (AAM)
ADC_3V3: C45.1, U9.3 (OUT); also elsewhere on the board
CS1: R18.2, U8.10 (CS1)
CS2: R19.2, U8.15 (CS2)
CS-DIS: R17.2, U8.12 (CS_DIS)
EN: R16.2, U7.17 (EN)
EN-PWR: R16.1, S3.2 (COMMON), U8.9 (IN1), U8.16 (IN2)
EN-PWR-PRE: R13.1, R14.2, S3.1 (A)
FB: R20.1, R21.2, U7.1 (FB)
GND: C41.2, C42.2, C44.2, C45.2, C49.2, D4.C (K), D5.C (K), D7.C (K), J6.2, R14.1, R15.1, R17.1, R18.1, R19.1, R21.1, S3.3 (B), U7.3 (AGND), U7.12 (PGND), U7.13 (PGND), U7.14 (PGND), U8.13 (GND), U9.1 (GND), U13.2 (GND); also elsewhere on the board
SW: U7.456 (SW)
VBATT: U8.1 (OUT2), U8.2 (OUT2), U8.3 (OUT2), U8.4 (OUT2), U8.5 (OUT1), U8.6 (OUT1), U8.7 (OUT1), U8.8 (OUT1), XF1.1, XF1.2 (1)
VIN: J6.1, R13.2, U8.17 (VCC)

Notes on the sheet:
Zener diode added on 5v so no back current from MBED when no battery power
Not connected on purpose
Low Dropout Regulators (LDO)
Double Channel High Side Driver

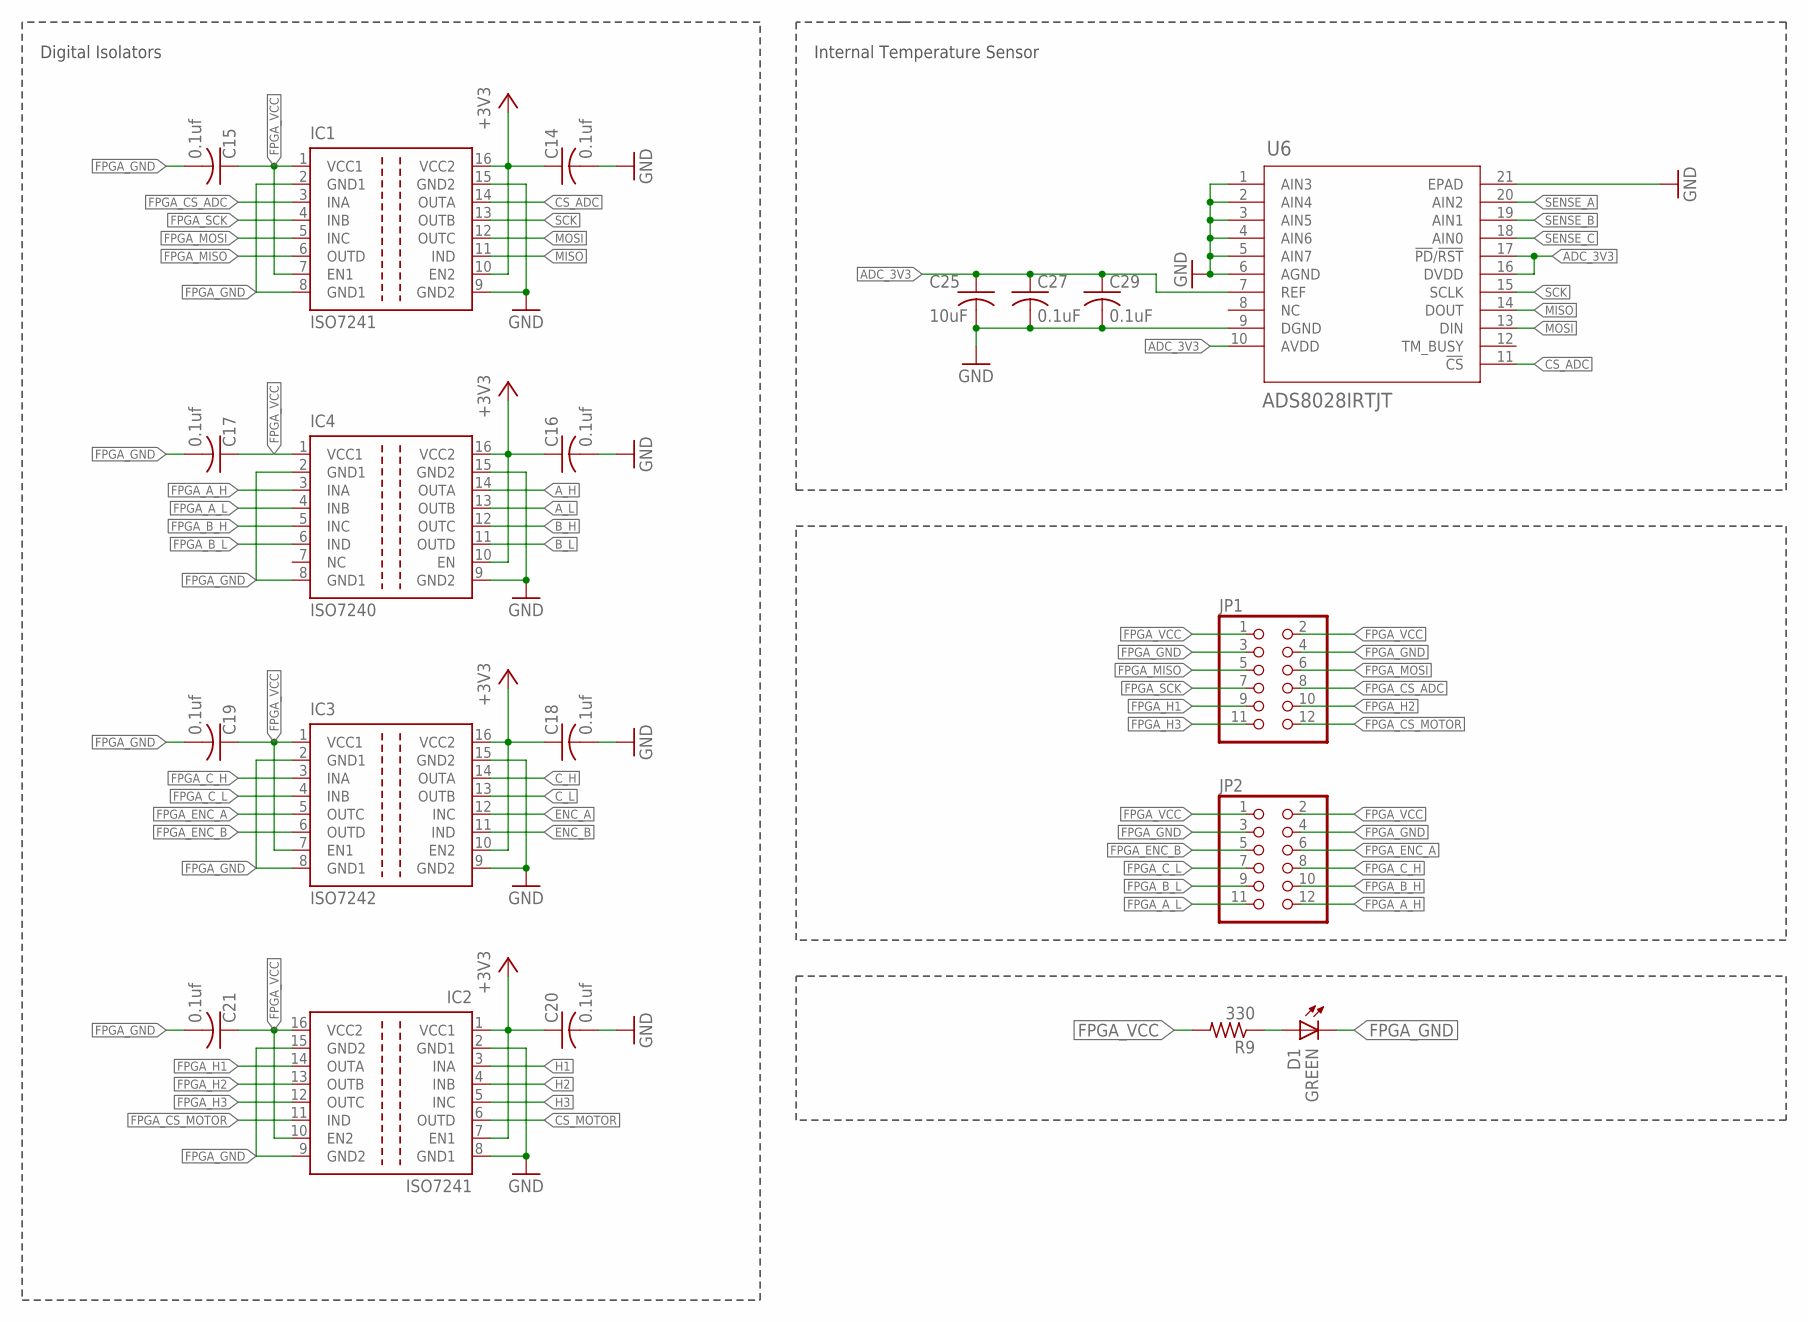
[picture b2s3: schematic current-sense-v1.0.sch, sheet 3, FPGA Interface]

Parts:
C14, C15, C16, C17, C18, C19, C20, C21: 0.1uf; C0603
C25: 10uF; C0603
C27, C29: 0.1uF; C0603
D1: GREEN; CHIP-LED0603
IC1, IC2: ISO7241; SO-16DW
IC3: ISO7242; SO-16DW
IC4: ISO7240; SO-16DW
JP1, JP2: PINHD-2X6/90; 2X06/90
R9: 330; R0603
U6: ADS8028IRTJT; RTJ20_2P7X2P7; DIGIKEY 296-30382-2-ND

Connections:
+3V3: C14.1, C16.1, C18.1, C20.1, IC1.10 (EN2), IC1.16 (VCC2), IC2.1 (VCC1), IC2.7 (EN1), IC3.10 (EN2), IC3.16 (VCC2), IC4.10 (EN), IC4.16 (VCC2); also elsewhere on the board
ADC_3V3: C25.1, C27.1, C29.1, U6.7 (REF), U6.10 (AVDD), U6.16 (DVDD), U6.17 (!PD!/!RST!); also elsewhere on the board
A_H: IC4.14 (OUTA); also elsewhere on the board
A_L: IC4.13 (OUTB); also elsewhere on the board
B_H: IC4.12 (OUTC); also elsewhere on the board
B_L: IC4.11 (OUTD); also elsewhere on the board
CS_ADC: IC1.14 (OUTA), U6.11 (!CS)
CS_MOTOR: IC2.6 (OUTD); also elsewhere on the board
C_H: IC3.14 (OUTA); also elsewhere on the board
C_L: IC3.13 (OUTB); also elsewhere on the board
ENC_A: IC3.12 (INC); also elsewhere on the board
ENC_B: IC3.11 (IND); also elsewhere on the board
FPGA_A_H: IC4.3 (INA), JP2.12
FPGA_A_L: IC4.4 (INB), JP2.11
FPGA_B_H: IC4.5 (INC), JP2.10
FPGA_B_L: IC4.6 (IND), JP2.9
FPGA_CS_ADC: IC1.3 (INA), JP1.8
FPGA_CS_MOTOR: IC2.11 (IND), JP1.12
FPGA_C_H: IC3.3 (INA), JP2.8
FPGA_C_L: IC3.4 (INB), JP2.7
FPGA_ENC_A: IC3.5 (OUTC), JP2.6
FPGA_ENC_B: IC3.6 (OUTD), JP2.5
FPGA_GND: C15.2, C17.2, C19.2, C21.2, D1.C (K), IC1.2 (GND1), IC1.8 (GND1), IC2.9 (GND2), IC2.15 (GND2), IC3.2 (GND1), IC3.8 (GND1), IC4.2 (GND1), IC4.8 (GND1), JP1.3, JP1.4, JP2.3, JP2.4
FPGA_H1: IC2.14 (OUTA), JP1.9
FPGA_H2: IC2.13 (OUTB), JP1.10
FPGA_H3: IC2.12 (OUTC), JP1.11
FPGA_MISO: IC1.6 (OUTD), JP1.5
FPGA_MOSI: IC1.5 (INC), JP1.6
FPGA_SCK: IC1.4 (INB), JP1.7
FPGA_VCC: C15.1, C17.1, C19.1, C21.1, IC1.1 (VCC1), IC1.7 (EN1), IC2.10 (EN2), IC2.16 (VCC2), IC3.1 (VCC1), IC3.7 (EN1), IC4.1 (VCC1), JP1.1, JP1.2, JP2.1, JP2.2, R9.2
GND: C14.2, C16.2, C18.2, C20.2, C25.2, C27.2, C29.2, IC1.9 (GND2), IC1.15 (GND2), IC2.2 (GND1), IC2.8 (GND1), IC3.9 (GND2), IC3.15 (GND2), IC4.9 (GND2), IC4.15 (GND2), U6.1 (AIN3), U6.2 (AIN4), U6.3 (AIN5), U6.4 (AIN6), U6.5 (AIN7), U6.6 (AGND), U6.9 (DGND), U6.21 (EPAD); also elsewhere on the board
H1: IC2.3 (INA); also elsewhere on the board
H2: IC2.4 (INB); also elsewhere on the board
H3: IC2.5 (INC); also elsewhere on the board
MISO: IC1.11 (IND), U6.14 (DOUT); also elsewhere on the board
MOSI: IC1.12 (OUTC), U6.13 (DIN); also elsewhere on the board
unnamed: D1.A, R9.1
SCK: IC1.13 (OUTB), U6.15 (SCLK); also elsewhere on the board
SENSE_A: U6.20 (AIN2); also elsewhere on the board
SENSE_B: U6.19 (AIN1); also elsewhere on the board
SENSE_C: U6.18 (AIN0); also elsewhere on the board

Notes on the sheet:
Digital Isolators
Internal Temperature Sensor
